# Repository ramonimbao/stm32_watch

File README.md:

# DIY STM32-based Watch

This repository contains the necessary files for building your own STM32-based watch.

# Prerequisites

- [OpenOCD](https://gnu-mcu-eclipse.github.io/openocd/install/)
- [System Workbend for STM32](http://www.st.com/en/development-tools/sw4stm32.html)

# Assembly instructions

Details assembly instructions for the project are located in [BUILDING.md](BUILDING.md).

# License

This project is licensed under the MIT license - see the [LICENSE.md](LICENSE.md) for more details.

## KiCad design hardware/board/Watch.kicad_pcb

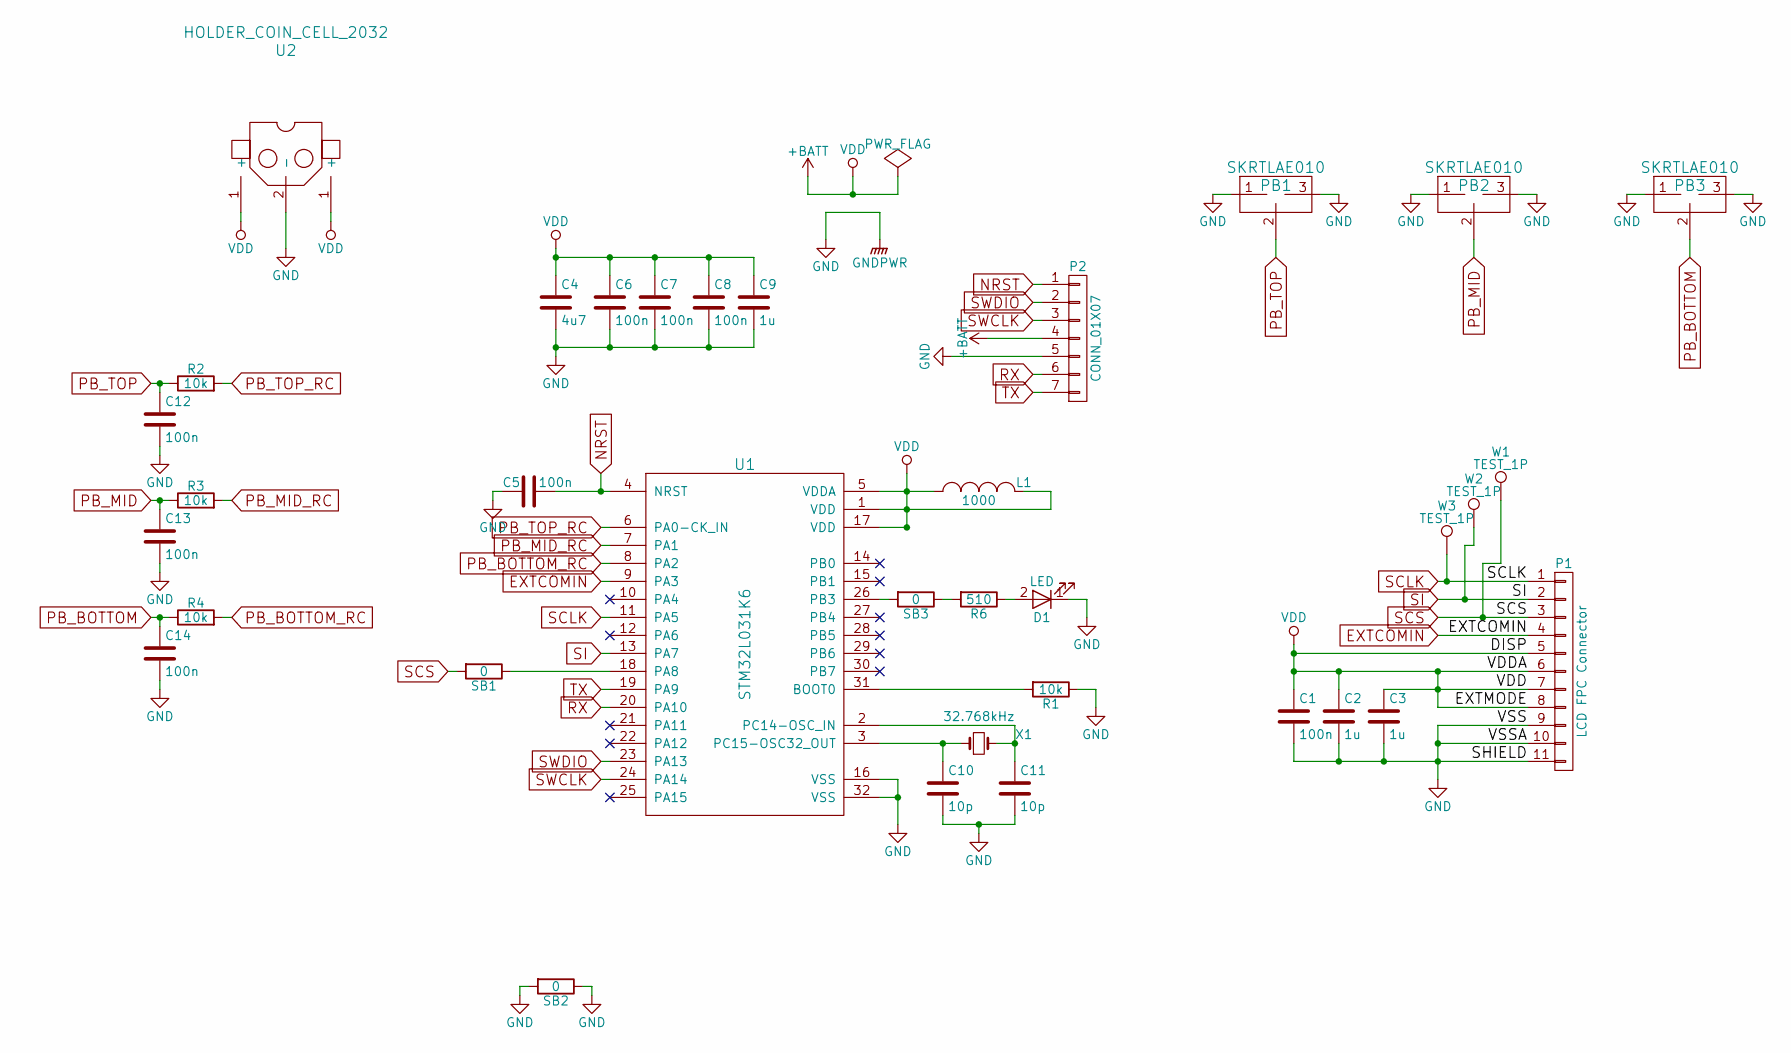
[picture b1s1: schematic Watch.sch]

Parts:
C1, C5, C6, C7, C8, C12, C13, C14: 100n; C_0805_HandSoldering
C2, C3, C9: 1u; C_0805_HandSoldering
C4: 4u7; C_0805_HandSoldering
C10, C11: 10p; C_0805_HandSoldering
D1: LED; LED_0805
L1: 1000; R_0805_HandSoldering
P1: LCD FPC Connector; FPC_10pin_0.5pitch
P2: CONN_01X07; Pin_Header_Straight_1x07_Pitch2.54mm
PB1, PB2, PB3: SKRTLAE010; SKTDLDE010
R1, R2, R3, R4: 10k; R_0805_HandSoldering
R6: 510; R_0805_HandSoldering
SB1, SB2, SB3: 0; R_0805_HandSoldering
U1: STM32L031K6; LQFP-32_7x7mm_Pitch0.8mm
U2: HOLDER_COIN_CELL_2032; HOLDER_COIN_CELL_2032_THROUGHHOLE
W1, W2, W3: TEST_1P; Measurement_Point_Round-TH_Small
X1: 32.768kHz; Crystal_3.2x1.5mm_HandSoldering

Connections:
+BATT: C1.1, C2.1, C3.1, C4.1, C6.1, C7.1, C8.1, C9.1, L1.1, L1.2, P1.5, P1.6, P1.7, P1.8, P2.4, U1.1 (VDD), U1.5 (VDDA), U1.17 (VDD), U2.1 (+)
EXTCOMIN: P1.4, U1.9 (PA3)
GND: C1.2, C2.2, C3.2, C4.2, C5.2, C6.2, C7.2, C8.2, C9.2, C10.2, C11.2, C12.2, C13.2, C14.2, D1.1 (K), P1.9, P1.10, P1.11, P2.5, PB1.1, PB1.3, PB2.1, PB2.3, PB3.1, PB3.3, R1.1, SB2.1, SB2.2, U1.16 (VSS), U1.32 (VSS), U2.2 (-)
NRST: C5.1, P2.1, U1.4 (NRST)
unnamed: C10.1, U1.3 (PC15-OSC32_OUT), X1.1
unnamed: C11.1, U1.2 (PC14-OSC_IN), X1.2
unnamed: D1.2 (A), R6.1
unnamed: R1.2, U1.31 (BOOT0)
unnamed: R6.2, SB3.1
unnamed: SB1.1, U1.18 (PA8)
unnamed: SB3.2, U1.26 (PB3)
PB_BOTTOM: C14.1, PB3.2, R4.1
PB_BOTTOM_RC: R4.2, U1.8 (PA2)
PB_MID: C13.1, PB2.2, R3.1
PB_MID_RC: R3.2, U1.7 (PA1)
PB_TOP: C12.1, PB1.2, R2.1
PB_TOP_RC: R2.2, U1.6 (PA0-CK_IN)
RX: P2.6, U1.20 (PA10)
SCLK: P1.1, U1.11 (PA5), W3.1
SCS: P1.3, SB1.2, W1.1
SI: P1.2, U1.13 (PA7), W2.1
SWCLK: P2.3, U1.24 (PA14)
SWDIO: P2.2, U1.23 (PA13)
TX: P2.7, U1.19 (PA9)

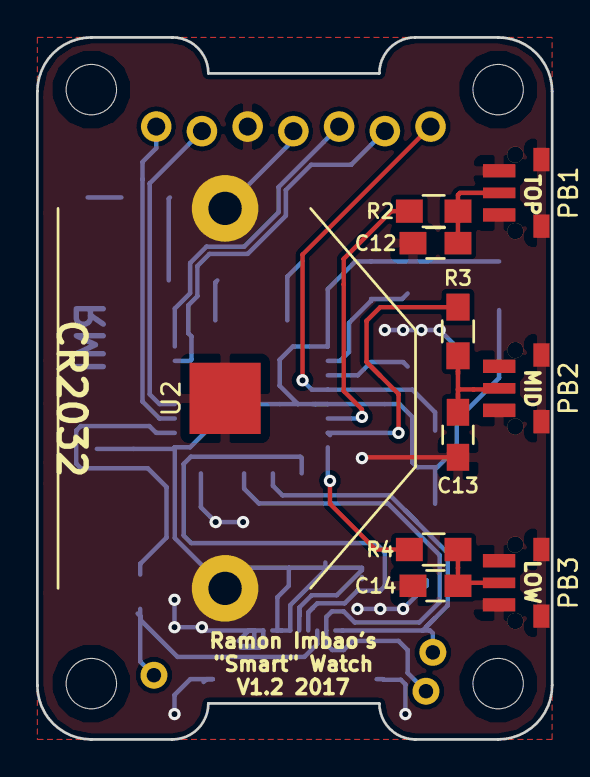
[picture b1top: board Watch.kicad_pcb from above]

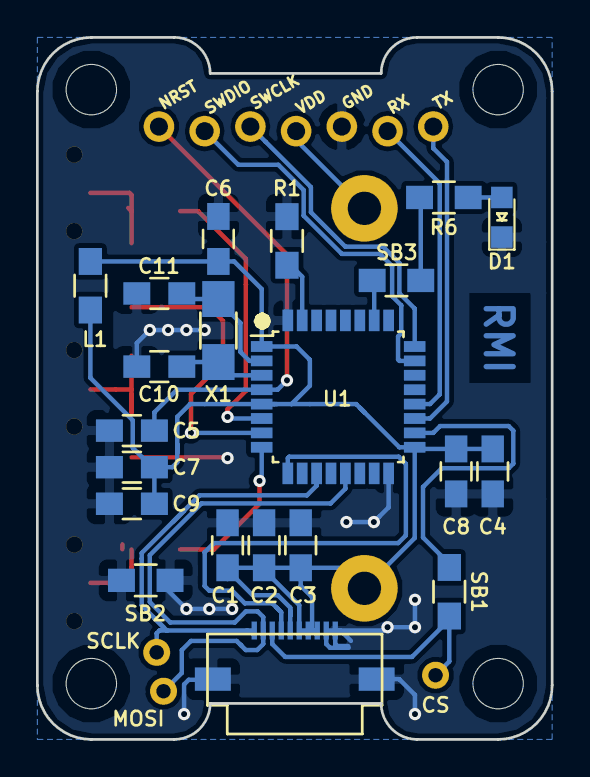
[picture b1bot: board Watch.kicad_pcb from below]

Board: 2 copper layers, 28.6 x 39.0 mm, 35 parts (25 on the bottom side), 24 nets.

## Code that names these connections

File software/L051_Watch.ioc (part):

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Mcu.Name=STM32L051K(6-8)Tx
Mcu.Package=LQFP32
Mcu.UserName=STM32L051K8Tx
PA0.GPIOParameters=GPIO_PuPd,GPIO_Label,GPIO_ModeDefaultEXTI
PA0.GPIO_Label=PB_TOP
PA0.GPIO_ModeDefaultEXTI=GPIO_MODE_IT_FALLING
PA0.GPIO_PuPd=GPIO_PULLUP
PA0.Signal=GPXTI0
PA1.GPIOParameters=GPIO_PuPd,GPIO_Label,GPIO_ModeDefaultEXTI
PA1.GPIO_Label=PB_MID
PA1.GPIO_ModeDefaultEXTI=GPIO_MODE_IT_FALLING
PA1.GPIO_PuPd=GPIO_PULLUP
PA1.Signal=GPXTI1
PA13.Mode=Serial_Wire
PA13.Signal=SYS_SWDIO
PA14.Mode=Serial_Wire
PA14.Signal=SYS_SWCLK
PA2.GPIOParameters=GPIO_PuPd,GPIO_Label,GPIO_ModeDefaultEXTI
PA2.GPIO_Label=PB_LOW
PA2.GPIO_ModeDefaultEXTI=GPIO_MODE_IT_FALLING
PA2.GPIO_PuPd=GPIO_PULLUP
PA2.Signal=GPXTI2
PA3.GPIOParameters=GPIO_PuPd,GPIO_Label
PA3.GPIO_Label=EXTCOMIN
PA3.GPIO_PuPd=GPIO_PULLDOWN
PA3.Signal=GPIO_Output
PA5.GPIOParameters=GPIO_Label
PA5.GPIO_Label=LCD_SCLK
PA5.Mode=TX_Only_Simplex_Unidirect_Master
PA5.Signal=SPI1_SCK
PA7.GPIOParameters=GPIO_Label
PA7.GPIO_Label=LCD_SI
PA7.Mode=TX_Only_Simplex_Unidirect_Master
PA7.Signal=SPI1_MOSI
PA8.GPIOParameters=GPIO_PuPd,GPIO_Label
PA8.GPIO_Label=LCD_SCS
PA8.GPIO_PuPd=GPIO_PULLDOWN
PA8.Signal=GPIO_Output
PB3.GPIOParameters=GPIO_PuPd,GPIO_Label
PB3.GPIO_Label=LED
PB3.GPIO_PuPd=GPIO_PULLDOWN
PB3.Signal=GPIO_Output
PC14-OSC32_IN.Mode=LSE-External-Oscillator
PC14-OSC32_IN.Signal=RCC_OSC32_IN
PC15-OSC32_OUT.Mode=LSE-External-Oscillator
PC15-OSC32_OUT.Signal=RCC_OSC32_OUT
RCC.SYSCLKFreq_VALUE=2097000
board=L051_Watch
